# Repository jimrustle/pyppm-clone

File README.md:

#

This project is a modern update of [https://github.com/geekysuavo/pyppm](https://github.com/geekysuavo/pyppm).

All design credits go to geekysuavo.

see kicad/ppm-clone.pdf for schematic

# Changes

This project implements pyppm ver 2.2 in KiCAD 10.0 instead of gEDA.

- The CTX02-13665 and LT3439 have been replaced with a Wurth 78931812512 and TI SN6505BDBV due to the CTX02 becoming obsoleted

# Notes

No changes so far. Any parts changes will be performed in separate branches.

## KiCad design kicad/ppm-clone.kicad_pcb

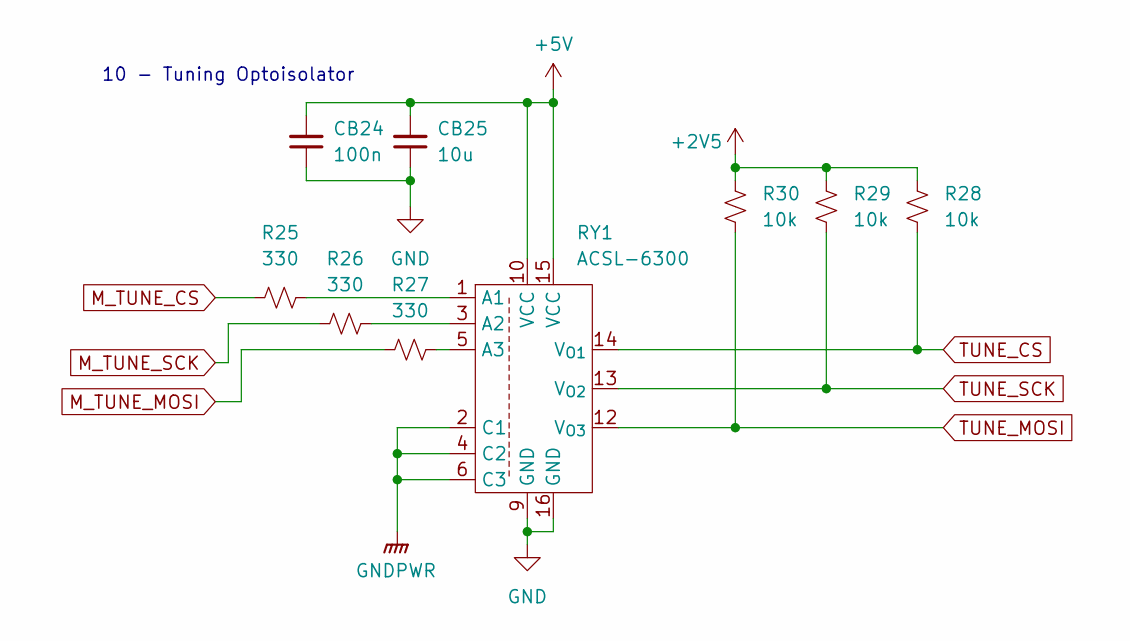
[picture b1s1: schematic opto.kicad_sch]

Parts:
CB24: 100n; C_0603_1608Metric_Pad1.08x0.95mm_HandSolder
CB25: 10u; C_0603_1608Metric_Pad1.08x0.95mm_HandSolder
R25, R26, R27: 330; R_0603_1608Metric_Pad0.98x0.95mm_HandSolder
R28, R29, R30: 10k; R_0603_1608Metric_Pad0.98x0.95mm_HandSolder
RY1: ACSL-6300; SO-16_3.9x9.9mm_P1.27mm

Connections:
+2V5: R28.1, R29.1, R30.1; also elsewhere on the board
+5V: CB24.2, CB25.2, RY1.10 (VCC), RY1.15 (VCC); also elsewhere on the board
GND: CB24.1, CB25.1, RY1.9 (GND), RY1.16 (GND); also elsewhere on the board
GNDPWR: RY1.2 (C1), RY1.4 (C2), RY1.6 (C3); also elsewhere on the board
M_TUNE_CS: R25.2; also elsewhere on the board
M_TUNE_MOSI: R27.2; also elsewhere on the board
M_TUNE_SCK: R26.2; also elsewhere on the board
unnamed: R25.1, RY1.1 (A1)
unnamed: R26.1, RY1.3 (A2)
unnamed: R27.1, RY1.5 (A3)
TUNE_CS: R28.2, RY1.14 (V_{O1}); also elsewhere on the board
TUNE_MOSI: R30.2, RY1.12 (V_{O3}); also elsewhere on the board
TUNE_SCK: R29.2, RY1.13 (V_{O2}); also elsewhere on the board

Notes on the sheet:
10 - Tuning Optoisolator

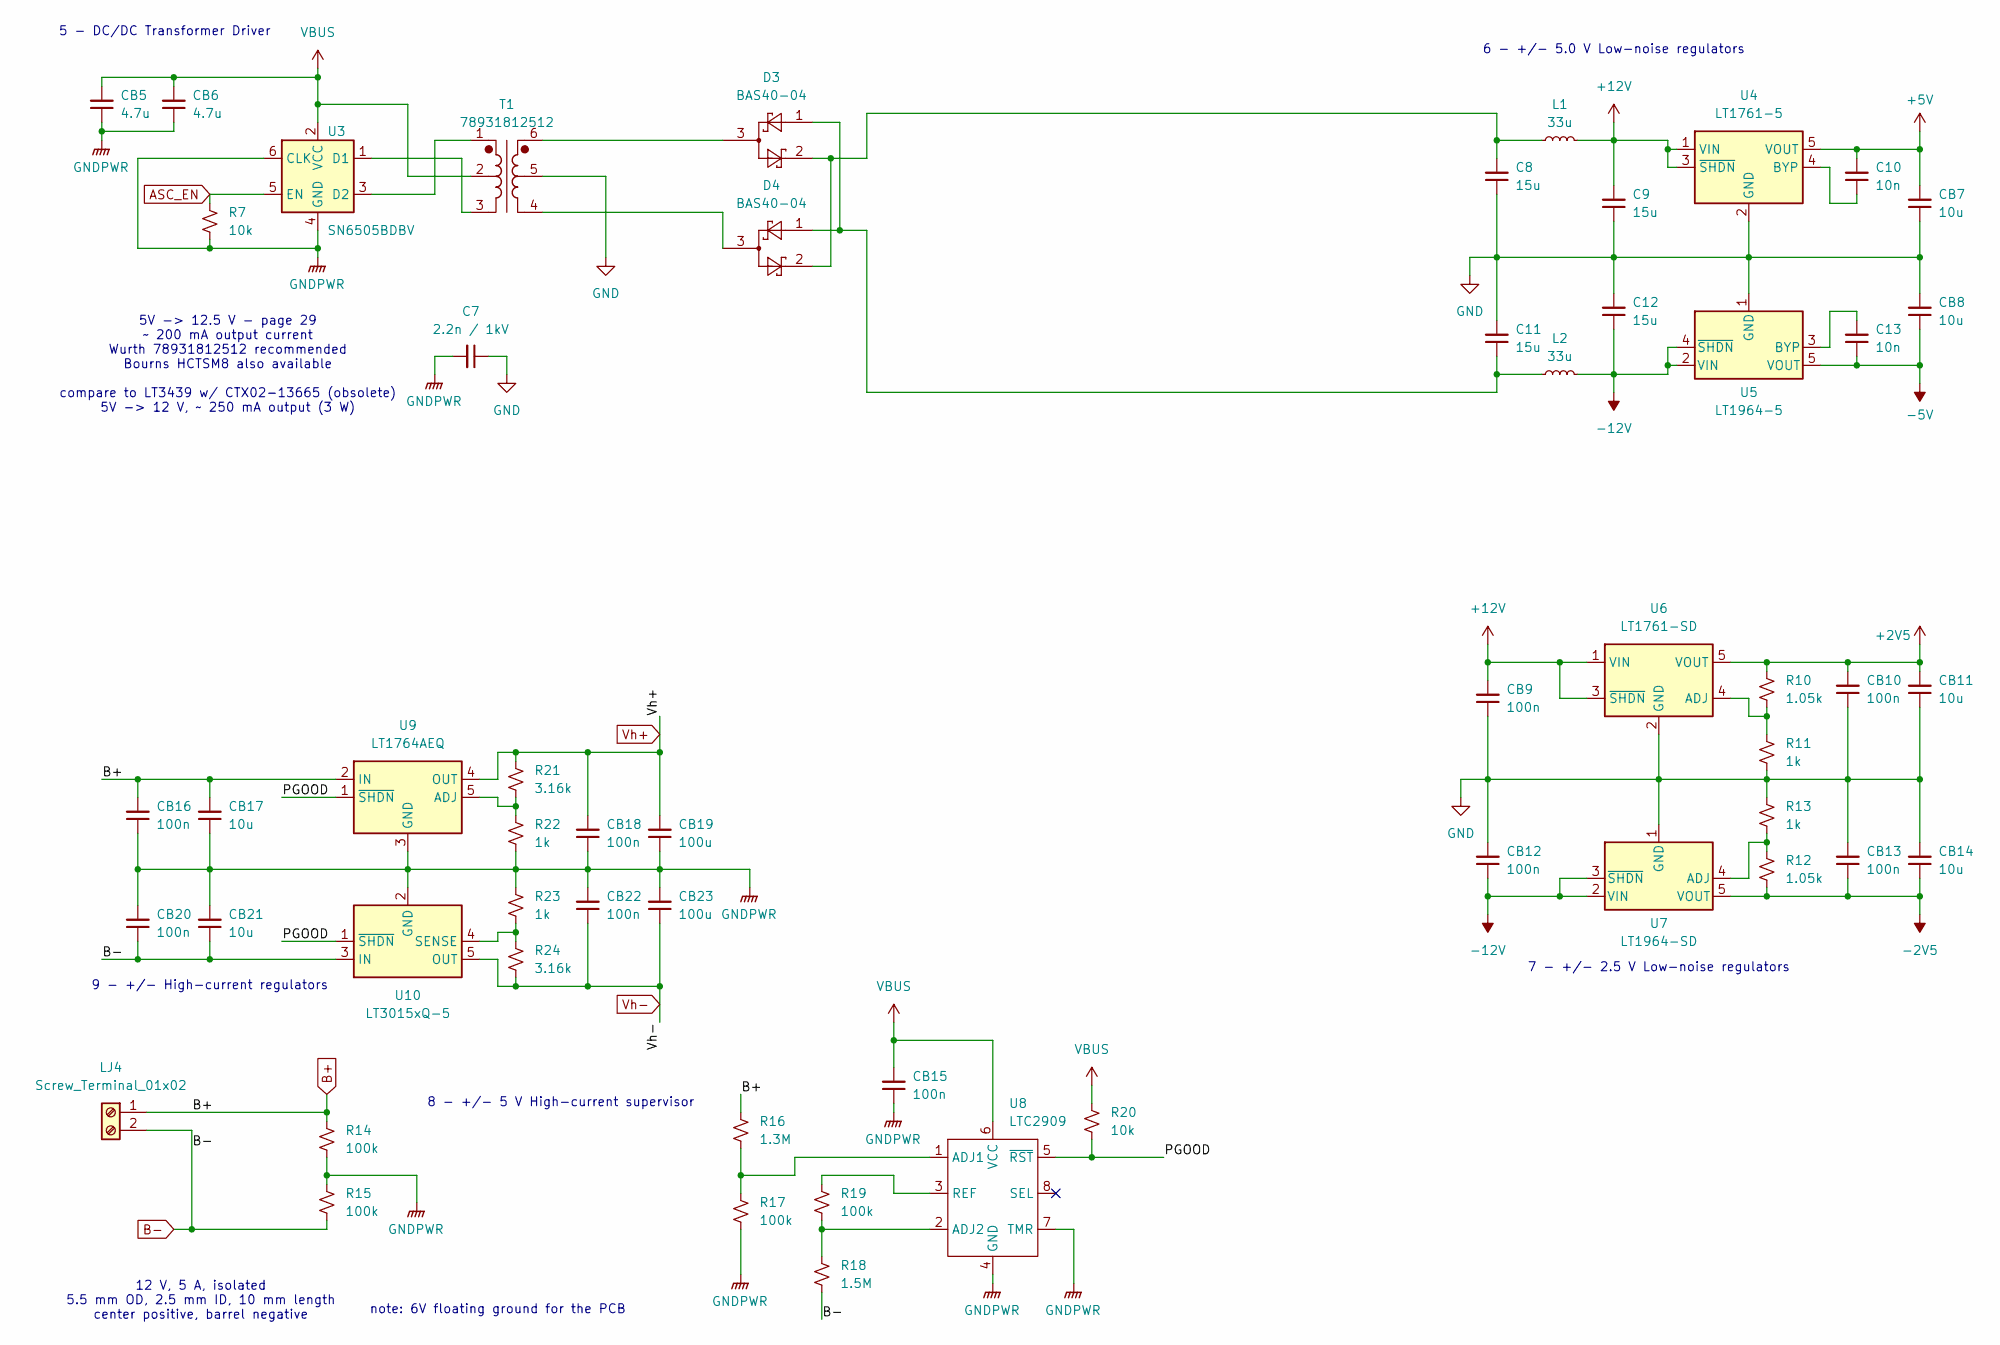
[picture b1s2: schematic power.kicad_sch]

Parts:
C7: 2.2n / 1kV; C_1206_3216Metric_Pad1.33x1.80mm_HandSolder
C8, C9, C11, C12: 15u; C_2220_5750Metric_Pad1.97x5.40mm_HandSolder
C10, C13: 10n; C_0603_1608Metric_Pad1.08x0.95mm_HandSolder
CB5, CB6: 4.7u; C_0603_1608Metric_Pad1.08x0.95mm_HandSolder
CB7, CB8, CB11, CB14, CB17, CB21: 10u; C_0603_1608Metric_Pad1.08x0.95mm_HandSolder
CB9, CB10, CB12, CB13, CB15, CB16, CB18, CB20, CB22: 100n; C_0603_1608Metric_Pad1.08x0.95mm_HandSolder
CB19, CB23: 100u; CP_Elec_5x5.3
D3, D4: BAS40-04; SOT-23
L1, L2: 33u; SDR6603
LJ4: Screw_Terminal_01x02; TerminalBlock_bornier-2_P5.08mm
R7, R20: 10k; R_0603_1608Metric_Pad0.98x0.95mm_HandSolder
R10, R12: 1.05k; R_0603_1608Metric_Pad0.98x0.95mm_HandSolder
R11, R13, R22, R23: 1k; R_0603_1608Metric_Pad0.98x0.95mm_HandSolder
R14, R15, R17, R19: 100k; R_0603_1608Metric_Pad0.98x0.95mm_HandSolder
R16: 1.3M; R_0603_1608Metric_Pad0.98x0.95mm_HandSolder
R18: 1.5M; R_0603_1608Metric_Pad0.98x0.95mm_HandSolder
R21, R24: 3.16k; R_0603_1608Metric_Pad0.98x0.95mm_HandSolder
T1: 78931812512; Transformer_Wuerth_750315371
U3: SN6505BDBV; SOT-23-6
U4: LT1761-5; TSOT-23-5
U5: LT1964-5; TSOT-23-5
U6: LT1761-SD; TSOT-23-5
U7: LT1964-SD; TSOT-23-5
U8: LTC2909; TSOT-23-8_HandSoldering
U9: LT1764AEQ; TO-263-5_TabPin3
U10: LT3015xQ-5; TO-263-5_TabPin3

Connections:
+2V5: CB10.2, CB11.2, R10.1, U6.5 (VOUT); also elsewhere on the board
+5V: C10.2, CB7.2, U4.5 (VOUT); also elsewhere on the board
+12V: C9.2, CB9.2, L1.2, U4.1 (VIN), U4.3 (~SHDN), U6.1 (VIN), U6.3 (~SHDN)
-2V5: CB13.1, CB14.1, R12.2, U7.5 (VOUT); also elsewhere on the board
-5V: C13.1, CB8.1, U5.5 (VOUT); also elsewhere on the board
-12V: C12.1, CB12.1, L2.2, U5.2 (VIN), U5.4 (~SHDN), U7.2 (VIN), U7.3 (~SHDN)
/power/PGOOD: R20.2, U8.5 (~RST), U9.1 (~SHDN), U10.1 (~SHDN)
ASC_EN: R7.1, U3.5 (EN); also elsewhere on the board
B+: CB16.2, CB17.2, LJ4.1, R14.1, R16.1, U9.2 (IN); also elsewhere on the board
B-: CB20.1, CB21.1, LJ4.2, R15.2, R18.2, U10.3 (IN)
GND: C7.1, C8.1, C9.1, C11.2, C12.2, CB7.1, CB8.2, CB9.1, CB10.1, CB11.1, CB12.2, CB13.2, CB14.2, R11.2, R13.1, T1.5, U4.2 (GND), U5.1 (GND), U6.2 (GND), U7.1 (GND); also elsewhere on the board
GNDPWR: C7.2, CB5.1, CB6.1, CB15.1, CB16.1, CB17.1, CB18.1, CB19.1, CB20.2, CB21.2, CB22.2, CB23.2, R7.2, R14.2, R15.1, R17.2, R22.2, R23.1, U3.4 (GND), U3.6 (CLK), U8.4 (GND), U8.7 (TMR), U9.3 (GND), U10.2 (GND); also elsewhere on the board
unnamed: C8.2, D3.2, D4.2, L1.1
unnamed: C11.1, D3.1, D4.1, L2.1
unnamed: D3.3, T1.6
unnamed: D4.3, T1.4
unnamed: T1.3, U3.1 (D1)
unnamed: T1.1, U3.3 (D2)
unnamed: C10.1, U4.4 (BYP)
unnamed: C13.2, U5.3 (BYP)
unnamed: R10.2, R11.1, U6.4 (ADJ)
unnamed: R12.1, R13.2, U7.4 (ADJ)
unnamed: R16.2, R17.1, U8.1 (ADJ1)
unnamed: R18.1, R19.2, U8.2 (ADJ2)
unnamed: R19.1, U8.3 (REF)
unnamed: R21.2, R22.1, U9.5 (ADJ)
unnamed: R23.2, R24.1, U10.4 (SENSE)
VBUS: CB5.2, CB6.2, CB15.2, R20.1, T1.2, U3.2 (VCC), U8.6 (VCC); also elsewhere on the board
Vh+: CB18.2, CB19.2, R21.1, U9.4 (OUT); also elsewhere on the board
Vh-: CB22.1, CB23.1, R24.2, U10.5 (OUT); also elsewhere on the board

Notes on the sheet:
8 - +/- 5 V High-current supervisor
9 - +/- High-current regulators
5V -> 12.5 V - page 29 ~ 200 mA output current Wurth 78931812512 recommended Bourns HCTSM8 also available compare to LT3439 w/ CTX02-13665 (obsolete) 5V -> 12 V, ~ 250 mA output (3 W)
7 - +/- 2.5 V Low-noise regulators
5 - DC/DC Transformer Driver
12 V, 5 A, isolated 5.5 mm OD, 2.5 mm ID, 10 mm length center positive, barrel negative
note: 6V floating ground for the PCB
6 - +/- 5.0 V Low-noise regulators

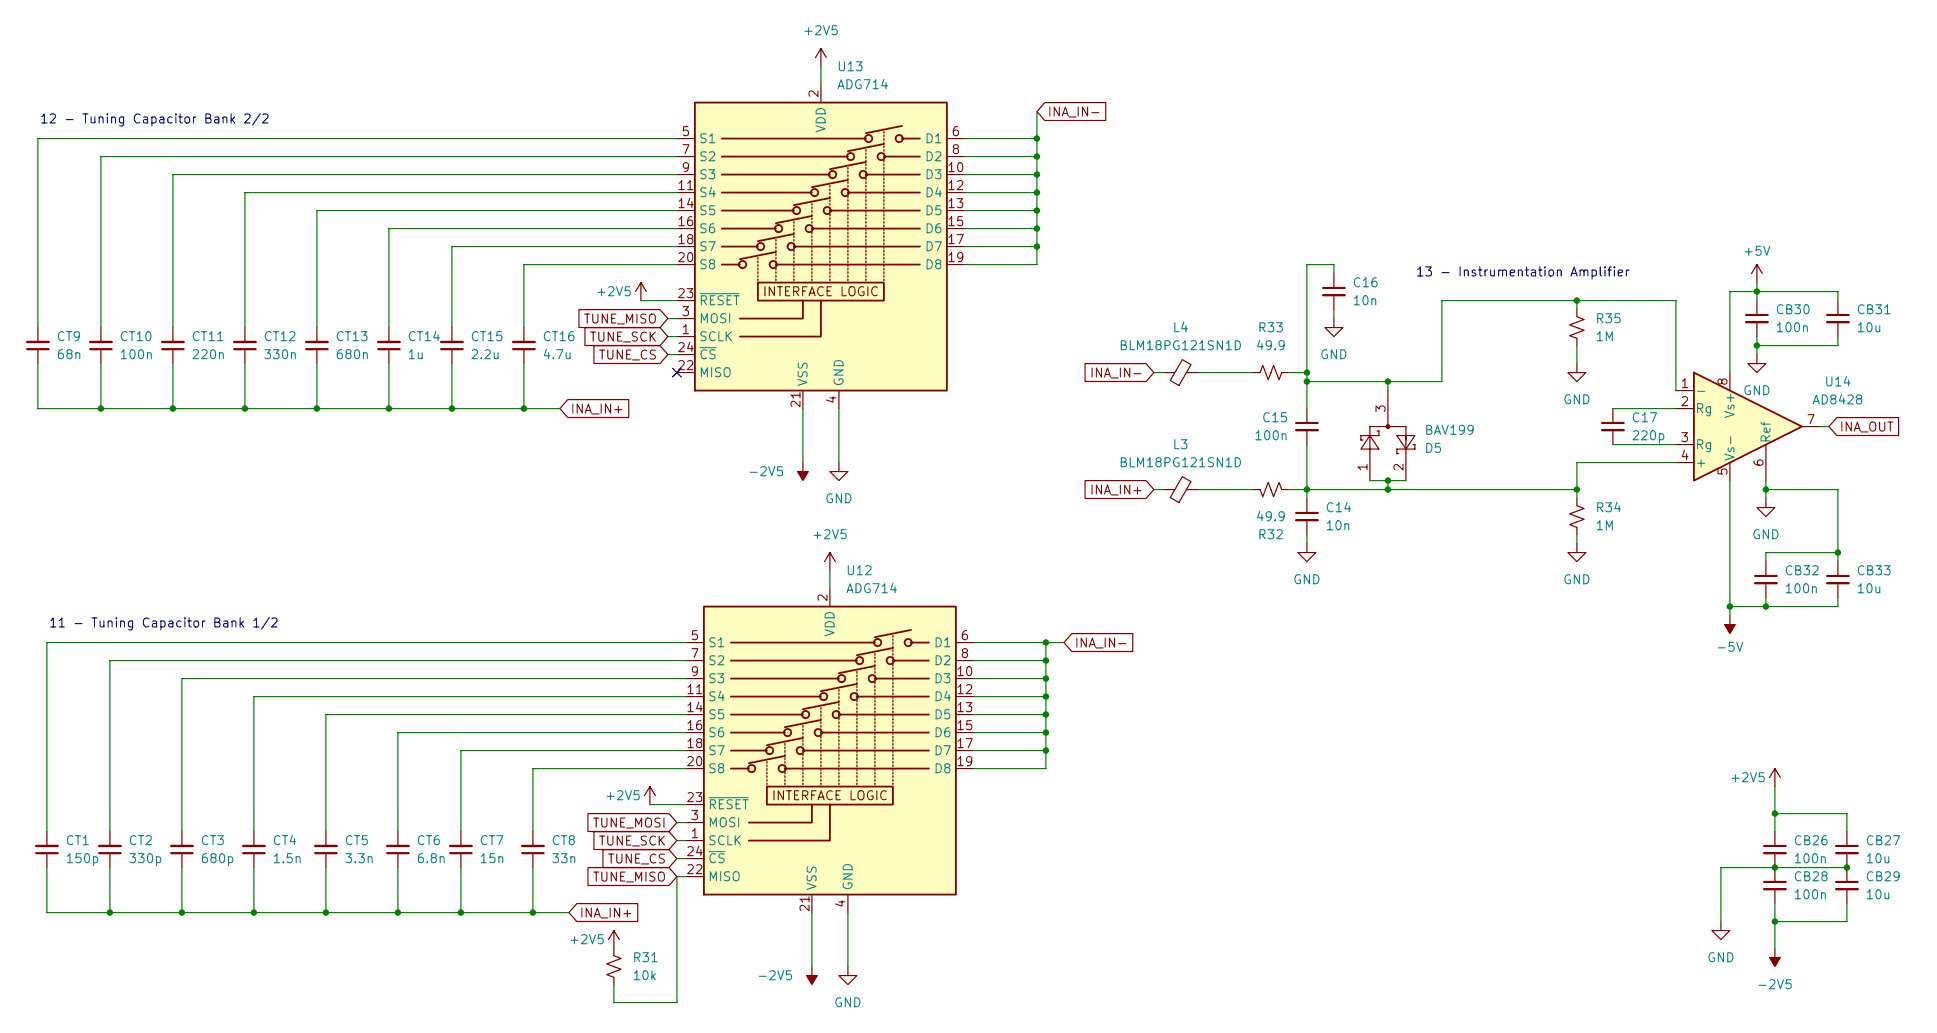
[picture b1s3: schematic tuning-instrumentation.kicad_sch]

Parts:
C14, C16: 10n; C_0603_1608Metric_Pad1.08x0.95mm_HandSolder
C15: 100n; C_0603_1608Metric_Pad1.08x0.95mm_HandSolder
C17: 220p; C_0603_1608Metric_Pad1.08x0.95mm_HandSolder
CB26, CB28, CB30, CB32: 100n; C_0603_1608Metric_Pad1.08x0.95mm_HandSolder
CB27, CB29, CB31, CB33: 10u; C_0603_1608Metric_Pad1.08x0.95mm_HandSolder
CT1: 150p; C_0603_1608Metric_Pad1.08x0.95mm_HandSolder
CT2: 330p; C_0603_1608Metric_Pad1.08x0.95mm_HandSolder
CT3: 680p; C_0603_1608Metric_Pad1.08x0.95mm_HandSolder
CT4: 1.5n; C_0603_1608Metric_Pad1.08x0.95mm_HandSolder
CT5: 3.3n; C_0603_1608Metric_Pad1.08x0.95mm_HandSolder
CT6: 6.8n; C_0603_1608Metric_Pad1.08x0.95mm_HandSolder
CT7: 15n; C_0603_1608Metric_Pad1.08x0.95mm_HandSolder
CT8: 33n; C_0603_1608Metric_Pad1.08x0.95mm_HandSolder
CT9: 68n; C_0603_1608Metric_Pad1.08x0.95mm_HandSolder
CT10: 100n; C_0603_1608Metric_Pad1.08x0.95mm_HandSolder
CT11: 220n; C_0603_1608Metric_Pad1.08x0.95mm_HandSolder
CT12: 330n; C_0603_1608Metric_Pad1.08x0.95mm_HandSolder
CT13: 680n; C_0603_1608Metric_Pad1.08x0.95mm_HandSolder
CT14: 1u; C_0603_1608Metric_Pad1.08x0.95mm_HandSolder
CT15: 2.2u; C_0603_1608Metric_Pad1.08x0.95mm_HandSolder
CT16: 4.7u; C_0603_1608Metric_Pad1.08x0.95mm_HandSolder
D5: BAV199; SOT-23
L3, L4: BLM18PG121SN1D; L_0603_1608Metric_Pad1.05x0.95mm_HandSolder
R31: 10k; R_0603_1608Metric_Pad0.98x0.95mm_HandSolder
R32, R33: 49.9; R_0603_1608Metric_Pad0.98x0.95mm_HandSolder
R34, R35: 1M; R_0603_1608Metric_Pad0.98x0.95mm_HandSolder
U12, U13: ADG714; TSSOP-24_4.4x7.8mm_P0.65mm
U14: AD8428; SOIC-8_3.9x4.9mm_P1.27mm

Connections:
+2V5: CB26.1, CB27.1, R31.2, U12.2 (VDD), U12.23 (~RESET), U13.2 (VDD), U13.23 (~RESET); also elsewhere on the board
+5V: CB30.1, CB31.1, U14.8 (Vs+); also elsewhere on the board
-2V5: CB28.2, CB29.2, U12.21 (VSS), U13.21 (VSS); also elsewhere on the board
-5V: CB32.2, CB33.2, U14.5 (Vs-); also elsewhere on the board
GND: C14.2, C16.2, CB26.2, CB27.2, CB28.1, CB29.1, CB30.2, CB31.2, CB32.1, CB33.1, R34.2, R35.2, U12.4 (GND), U13.4 (GND), U14.6 (Ref); also elsewhere on the board
INA_IN+: CT1.1, CT2.1, CT3.1, CT4.1, CT5.1, CT6.1, CT7.1, CT8.1, CT9.1, CT10.1, CT11.1, CT12.1, CT13.1, CT14.1, CT15.1, CT16.1, L3.1; also elsewhere on the board
INA_IN-: L4.1, U12.6 (D1), U12.8 (D2), U12.10 (D3), U12.12 (D4), U12.13 (D5), U12.15 (D6), U12.17 (D7), U12.19 (D8), U13.6 (D1), U13.8 (D2), U13.10 (D3), U13.12 (D4), U13.13 (D5), U13.15 (D6), U13.17 (D7), U13.19 (D8); also elsewhere on the board
INA_OUT: U14.7; also elsewhere on the board
unnamed: C17.1, U14.2 (Rg)
unnamed: C17.2, U14.3 (Rg)
unnamed: L3.2, R32.1
unnamed: L4.2, R33.1
unnamed: CT1.2, U12.5 (S1)
unnamed: CT2.2, U12.7 (S2)
unnamed: CT3.2, U12.9 (S3)
unnamed: CT4.2, U12.11 (S4)
unnamed: CT5.2, U12.14 (S5)
unnamed: CT6.2, U12.16 (S6)
unnamed: CT7.2, U12.18 (S7)
unnamed: CT8.2, U12.20 (S8)
unnamed: CT9.2, U13.5 (S1)
unnamed: CT10.2, U13.7 (S2)
unnamed: CT11.2, U13.9 (S3)
unnamed: CT12.2, U13.11 (S4)
unnamed: CT13.2, U13.14 (S5)
unnamed: CT14.2, U13.16 (S6)
unnamed: CT15.2, U13.18 (S7)
unnamed: CT16.2, U13.20 (S8)
unnamed: C14.1, C15.2, D5.1, D5.2, R32.2, R34.1, U14.4 (+)
unnamed: C15.1, C16.1, D5.3, R33.2, R35.1, U14.1 (-)
TUNE_CS: U12.24 (~CS), U13.24 (~CS); also elsewhere on the board
TUNE_MISO: R31.1, U12.22 (MISO), U13.3 (MOSI)
TUNE_MOSI: U12.3 (MOSI); also elsewhere on the board
TUNE_SCK: U12.1 (SCLK), U13.1 (SCLK); also elsewhere on the board

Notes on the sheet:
12 - Tuning Capacitor Bank 2/2
13 - Instrumentation Amplifier
11 - Tuning Capacitor Bank 1/2

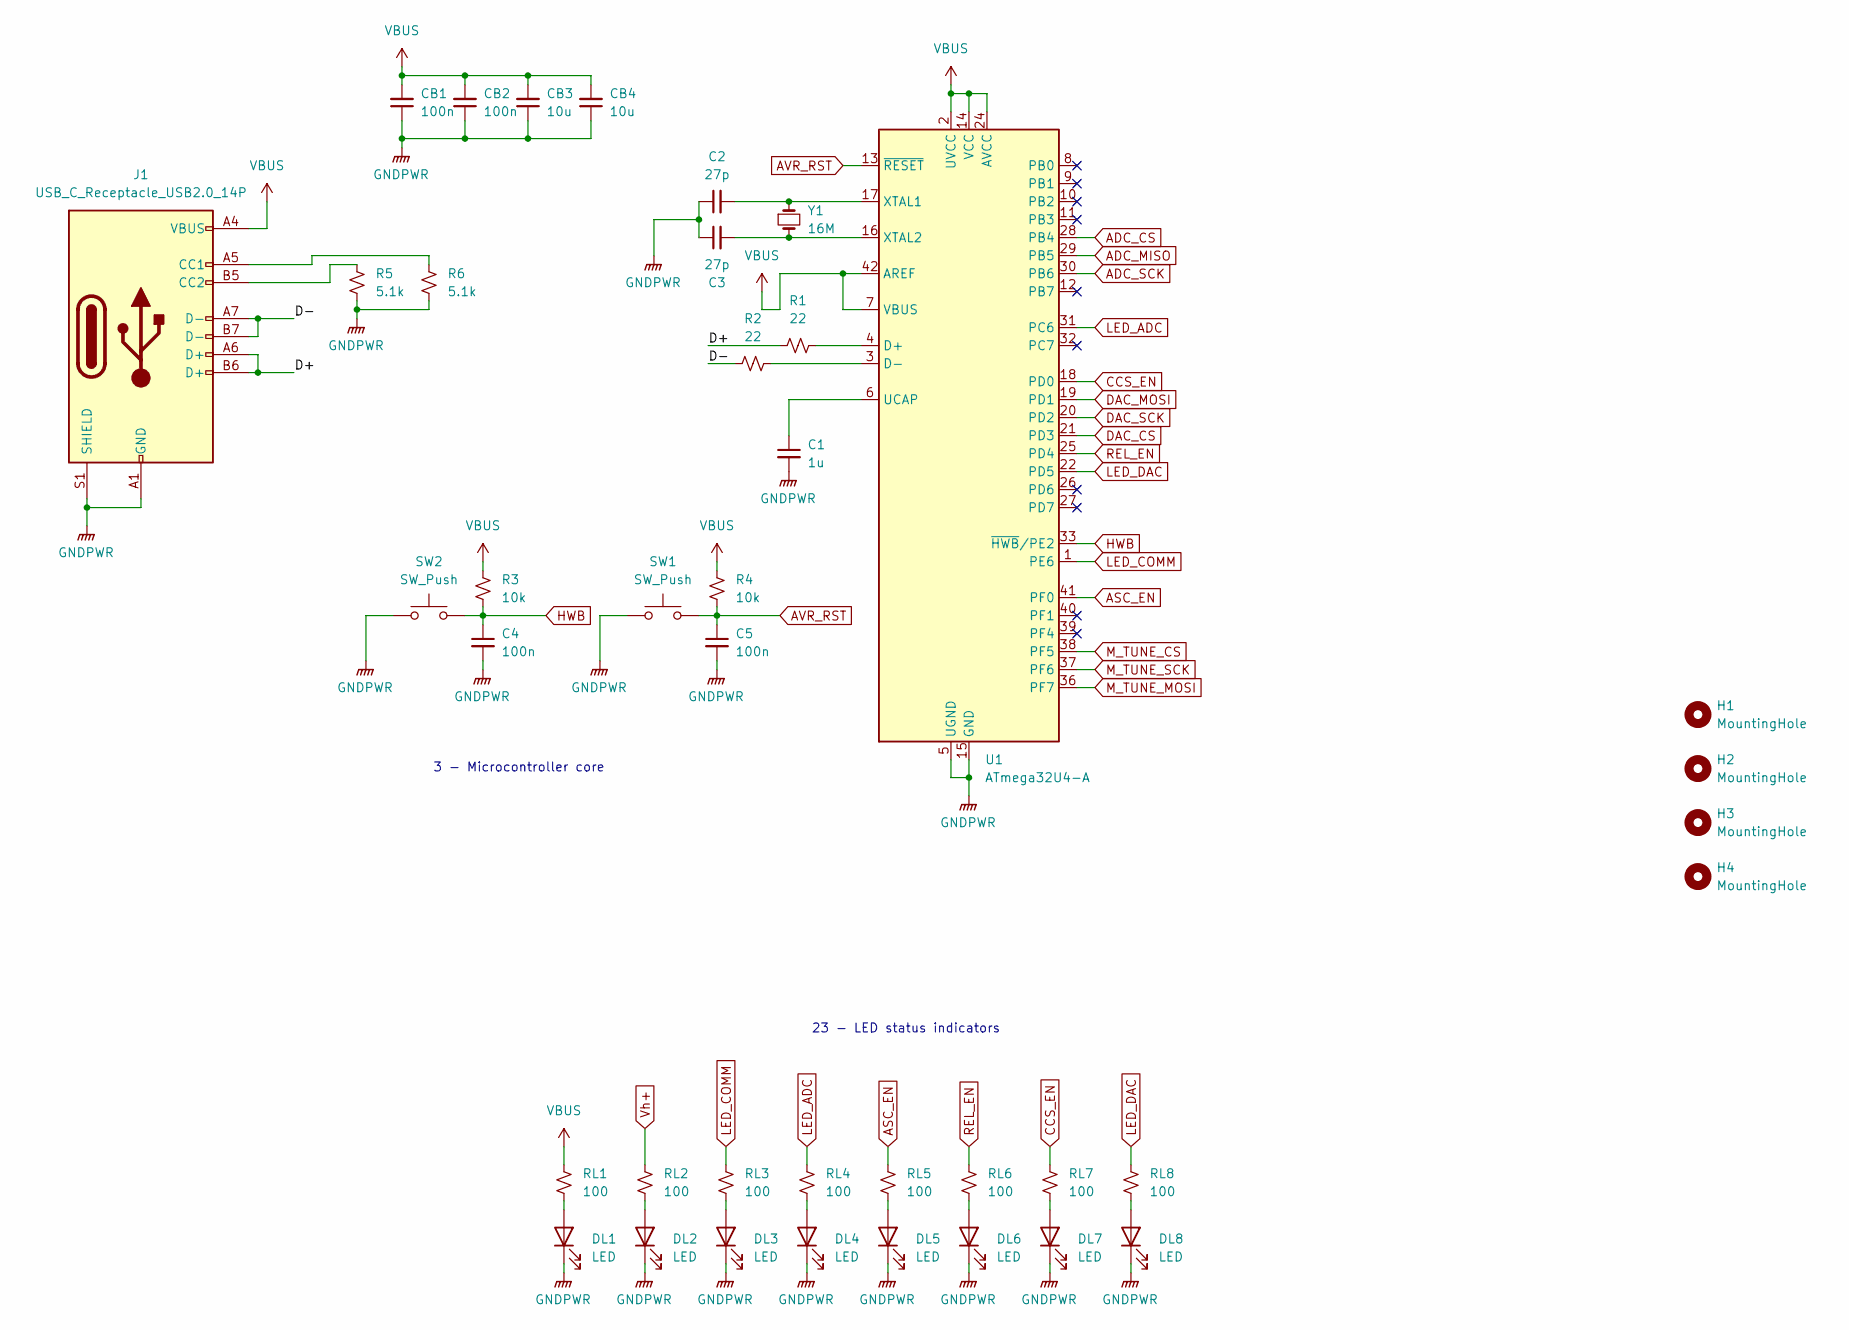
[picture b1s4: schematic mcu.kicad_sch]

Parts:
C1: 1u; C_0603_1608Metric_Pad1.08x0.95mm_HandSolder
C2, C3: 27p; C_0603_1608Metric_Pad1.08x0.95mm_HandSolder
C4, C5: 100n; C_0603_1608Metric_Pad1.08x0.95mm_HandSolder
CB1, CB2: 100n; C_0603_1608Metric_Pad1.08x0.95mm_HandSolder
CB3, CB4: 10u; C_0603_1608Metric_Pad1.08x0.95mm_HandSolder
DL1, DL2, DL3, DL4, DL5, DL6, DL7, DL8: LED; LED_0603_1608Metric_Pad1.05x0.95mm_HandSolder
H1, H2, H3, H4: MountingHole; MountingHole_3.2mm_M3_ISO7380_Pad
J1: USB_C_Receptacle_USB2.0_14P; USB_C_Receptacle_HCTL_HC-TYPE-C-16P-01A
R1, R2: 22; R_0603_1608Metric_Pad0.98x0.95mm_HandSolder
R3, R4: 10k; R_0603_1608Metric_Pad0.98x0.95mm_HandSolder
R5, R6: 5.1k; R_0603_1608Metric_Pad0.98x0.95mm_HandSolder
RL1, RL2, RL3, RL4, RL5, RL6, RL7, RL8: 100; R_0603_1608Metric_Pad0.98x0.95mm_HandSolder
SW1, SW2: SW_Push; SW_SPST_B3S-1000
U1: ATmega32U4-A; TQFP-44_10x10mm_P0.8mm
Y1: 16M; Crystal_SMD_Abracon_ABM7-2Pin_6.0x3.5mm

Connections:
/mcu/D+: J1.A6 (D+), J1.B6 (D+), R1.2
/mcu/D-: J1.A7 (D-), J1.B7 (D-), R2.2
ADC_CS: U1.28 (PB4); also elsewhere on the board
ADC_MISO: U1.29 (PB5); also elsewhere on the board
ADC_SCK: U1.30 (PB6); also elsewhere on the board
ASC_EN: RL5.1, U1.41 (PF0); also elsewhere on the board
AVR_RST: C5.1, R4.2, SW1.2, U1.13 (~RESET)
CCS_EN: RL7.1, U1.18 (PD0); also elsewhere on the board
DAC_CS: U1.21 (PD3); also elsewhere on the board
DAC_MOSI: U1.19 (PD1); also elsewhere on the board
DAC_SCK: U1.20 (PD2); also elsewhere on the board
GNDPWR: C1.2, C2.1, C3.1, C4.2, C5.2, CB1.1, CB2.1, CB3.1, CB4.1, DL1.1 (K), DL2.1 (K), DL3.1 (K), DL4.1 (K), DL5.1 (K), DL6.1 (K), DL7.1 (K), DL8.1 (K), J1.A1 (GND), J1.A12 (GND), J1.B1 (GND), J1.B12 (GND), J1.S1 (SHIELD), R5.2, R6.2, SW1.1, SW2.1, U1.5 (UGND), U1.15 (GND), U1.23 (GND), U1.35 (GND), U1.43 (GND); also elsewhere on the board
HWB: C4.1, R3.2, SW2.2, U1.33 (~HWB/PE2)
LED_ADC: RL4.1, U1.31 (PC6)
LED_COMM: RL3.1, U1.1 (PE6)
LED_DAC: RL8.1, U1.22 (PD5)
M_TUNE_CS: U1.38 (PF5); also elsewhere on the board
M_TUNE_MOSI: U1.36 (PF7); also elsewhere on the board
M_TUNE_SCK: U1.37 (PF6); also elsewhere on the board
unnamed: DL1.2 (A), RL1.2
unnamed: DL2.2 (A), RL2.2
unnamed: DL3.2 (A), RL3.2
unnamed: DL4.2 (A), RL4.2
unnamed: DL5.2 (A), RL5.2
unnamed: DL6.2 (A), RL6.2
unnamed: DL7.2 (A), RL7.2
unnamed: DL8.2 (A), RL8.2
unnamed: J1.A5 (CC1), R6.1
unnamed: J1.B5 (CC2), R5.1
unnamed: R1.1, U1.4 (D+)
unnamed: R2.1, U1.3 (D-)
unnamed: C1.1, U1.6 (UCAP)
unnamed: C2.2, U1.17 (XTAL1), Y1.1
unnamed: C3.2, U1.16 (XTAL2), Y1.2
REL_EN: RL6.1, U1.25 (PD4); also elsewhere on the board
VBUS: CB1.2, CB2.2, CB3.2, CB4.2, J1.A4 (VBUS), J1.A9 (VBUS), J1.B4 (VBUS), J1.B9 (VBUS), R3.1, R4.1, RL1.1, U1.2 (UVCC), U1.7 (VBUS), U1.14 (VCC), U1.24 (AVCC), U1.34 (VCC), U1.42 (AREF), U1.44 (AVCC); also elsewhere on the board
Vh+: RL2.1; also elsewhere on the board

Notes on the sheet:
23 - LED status indicators
3 - Microcontroller core

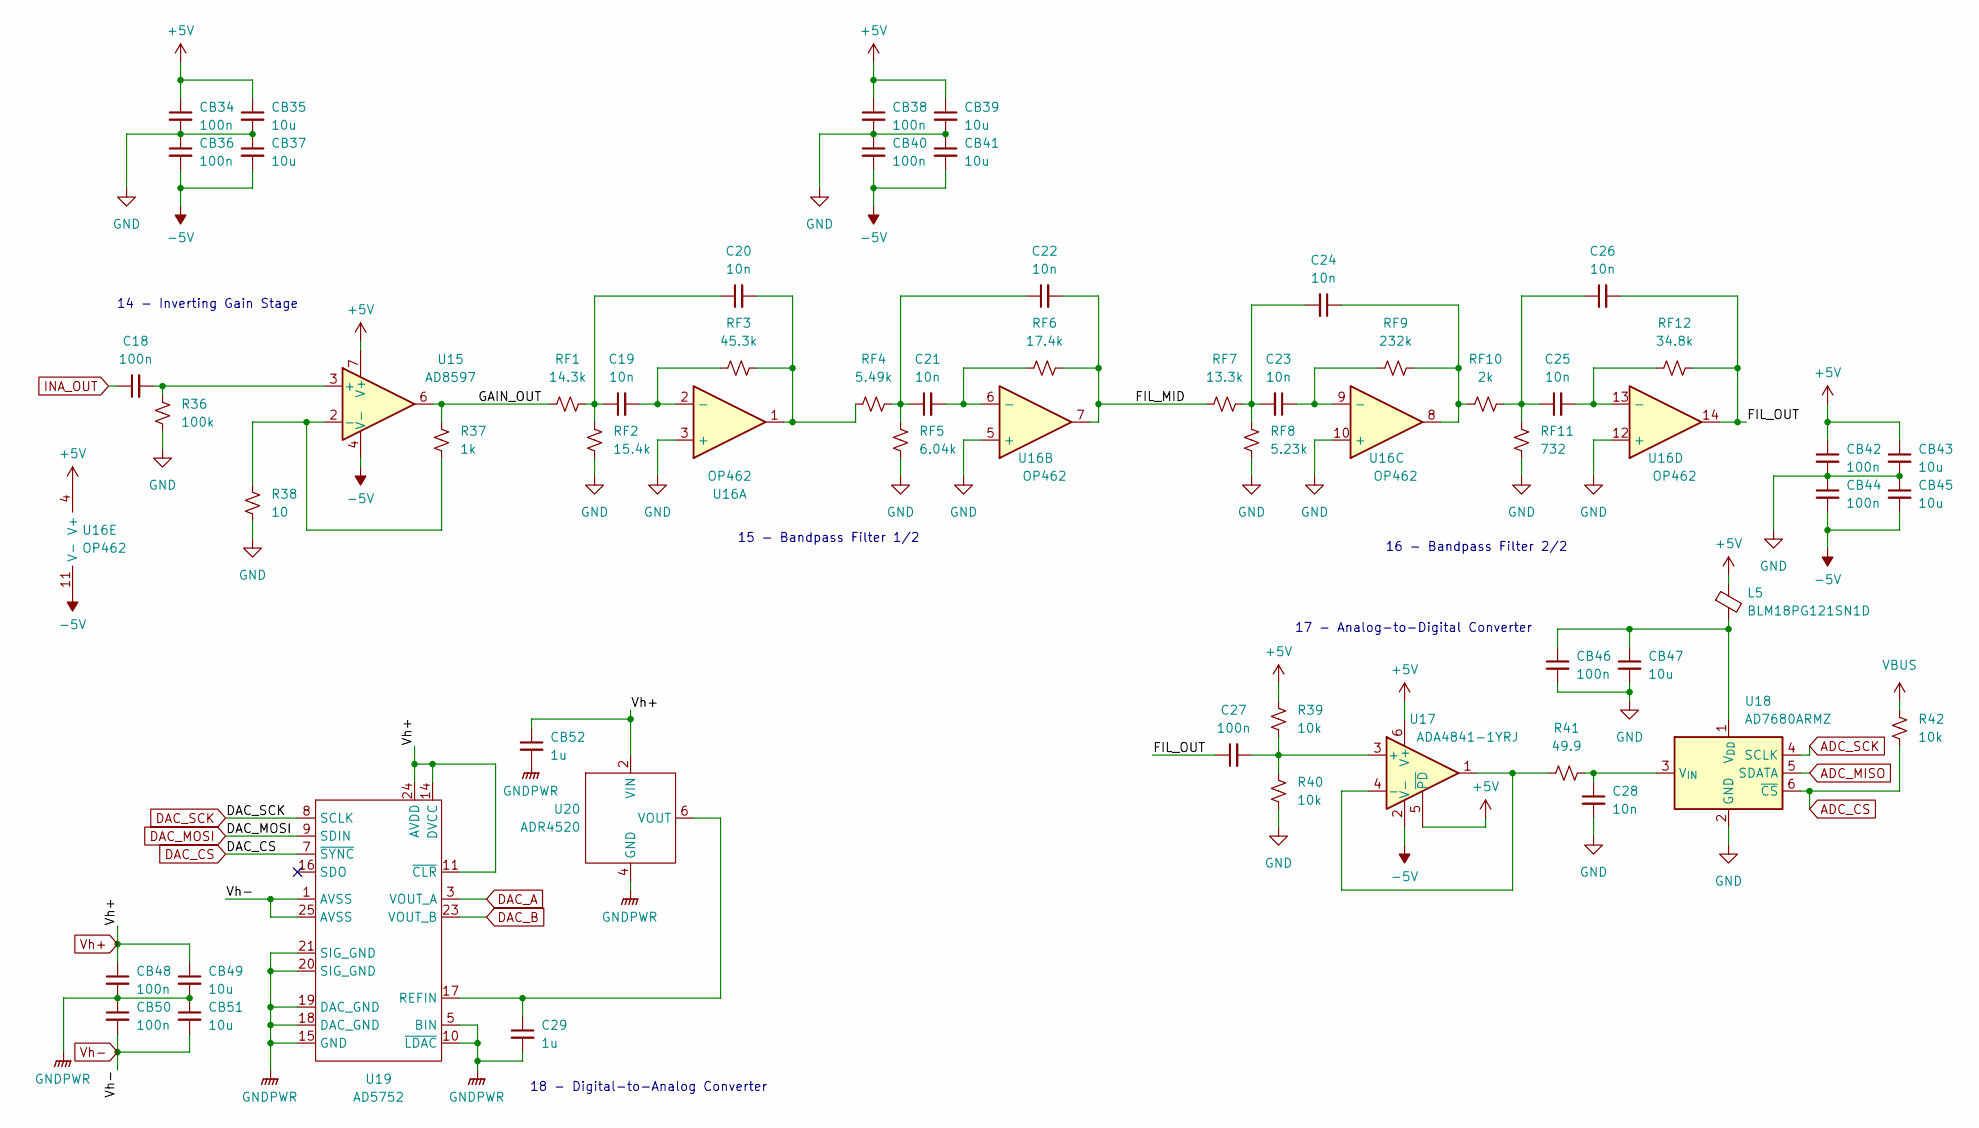
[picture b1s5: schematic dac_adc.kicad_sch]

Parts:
C18, C27: 100n; C_0603_1608Metric_Pad1.08x0.95mm_HandSolder
C19, C20, C21, C22, C23, C24, C25, C26, C28: 10n; C_0603_1608Metric_Pad1.08x0.95mm_HandSolder
C29: 1u; C_0603_1608Metric_Pad1.08x0.95mm_HandSolder
CB34, CB36, CB38, CB40, CB42, CB44, CB46, CB48, CB50: 100n; C_0603_1608Metric_Pad1.08x0.95mm_HandSolder
CB35, CB37, CB39, CB41, CB43, CB45, CB47, CB49, CB51: 10u; C_0603_1608Metric_Pad1.08x0.95mm_HandSolder
CB52: 1u; C_0603_1608Metric_Pad1.08x0.95mm_HandSolder
L5: BLM18PG121SN1D; L_0603_1608Metric_Pad1.05x0.95mm_HandSolder
R36: 100k; R_0603_1608Metric_Pad0.98x0.95mm_HandSolder
R37: 1k; R_0603_1608Metric_Pad0.98x0.95mm_HandSolder
R38: 10; R_0603_1608Metric_Pad0.98x0.95mm_HandSolder
R39, R40, R42: 10k; R_0603_1608Metric_Pad0.98x0.95mm_HandSolder
R41: 49.9; R_0603_1608Metric_Pad0.98x0.95mm_HandSolder
RF1: 14.3k; R_0603_1608Metric_Pad0.98x0.95mm_HandSolder
RF2: 15.4k; R_0603_1608Metric_Pad0.98x0.95mm_HandSolder
RF3: 45.3k; R_0603_1608Metric_Pad0.98x0.95mm_HandSolder
RF4: 5.49k; R_0603_1608Metric_Pad0.98x0.95mm_HandSolder
RF5: 6.04k; R_0603_1608Metric_Pad0.98x0.95mm_HandSolder
RF6: 17.4k; R_0603_1608Metric_Pad0.98x0.95mm_HandSolder
RF7: 13.3k; R_0603_1608Metric_Pad0.98x0.95mm_HandSolder
RF8: 5.23k; R_0603_1608Metric_Pad0.98x0.95mm_HandSolder
RF9: 232k; R_0603_1608Metric_Pad0.98x0.95mm_HandSolder
RF10: 2k; R_0603_1608Metric_Pad0.98x0.95mm_HandSolder
RF11: 732; R_0603_1608Metric_Pad0.98x0.95mm_HandSolder
RF12: 34.8k; R_0603_1608Metric_Pad0.98x0.95mm_HandSolder
U15: AD8597; SOIC-8_3.9x4.9mm_P1.27mm
U16: OP462; TSSOP-14_4.4x5mm_P0.65mm
U17: ADA4841-1YRJ; SOT-23-6
U18: AD7680ARMZ; SOT-23-6
U19: AD5752; HTSSOP-24-1EP_4.4x7.8mm_P0.65mm_EP3.2x5mm
U20: ADR4520; SOIC-8_3.9x4.9mm_P1.27mm

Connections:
+5V: CB34.1, CB35.1, CB38.1, CB39.1, CB42.1, CB43.1, L5.1, R39.1, U15.7 (V+), U16.4 (V+), U17.5 (~PD), U17.6 (V+); also elsewhere on the board
-5V: CB36.2, CB37.2, CB40.2, CB41.2, CB44.2, CB45.2, U15.4 (V-), U16.11 (V-), U17.2 (V-); also elsewhere on the board
/dac_adc/FIL_MID: C22.2, RF6.2, RF7.1, U16.7
/dac_adc/FIL_OUT: C26.2, C27.1, RF12.2, U16.14
/dac_adc/GAIN_OUT: R37.2, RF1.1, U15.6
ADC_CS: R42.2, U18.6 (~CS); also elsewhere on the board
ADC_MISO: U18.5 (SDATA); also elsewhere on the board
ADC_SCK: U18.4 (SCLK); also elsewhere on the board
DAC_A: U19.3 (VOUT_A); also elsewhere on the board
DAC_B: U19.23 (VOUT_B); also elsewhere on the board
DAC_CS: U19.7 (~SYNC); also elsewhere on the board
DAC_MOSI: U19.9 (SDIN); also elsewhere on the board
DAC_SCK: U19.8 (SCLK); also elsewhere on the board
GND: C28.2, CB34.2, CB35.2, CB36.1, CB37.1, CB38.2, CB39.2, CB40.1, CB41.1, CB42.2, CB43.2, CB44.1, CB45.1, CB46.2, CB47.2, R36.1, R38.1, R40.2, RF2.2, RF5.2, RF8.2, RF11.2, U16.3 (+), U16.5 (+), U16.10 (+), U16.12 (+), U18.2 (GND); also elsewhere on the board
GNDPWR: C29.2, CB48.2, CB49.2, CB50.1, CB51.1, CB52.2, U19.5 (BIN), U19.10 (~LDAC), U19.15 (GND), U19.18 (DAC_GND), U19.19 (DAC_GND), U19.20 (SIG_GND), U19.21 (SIG_GND), U20.4 (GND); also elsewhere on the board
INA_OUT: C18.1; also elsewhere on the board
unnamed: C19.1, C20.1, RF1.2, RF2.1
unnamed: C20.2, RF3.2, RF4.1, U16.1
unnamed: C21.1, C22.1, RF4.2, RF5.1
unnamed: C23.2, C24.2, RF7.2, RF8.1
unnamed: C24.1, RF9.2, RF10.1, U16.8
unnamed: C25.1, C26.1, RF10.2, RF11.1
unnamed: C18.2, R36.2, U15.3 (+)
unnamed: R37.1, R38.2, U15.2 (-)
unnamed: C19.2, RF3.1, U16.2 (-)
unnamed: C21.2, RF6.1, U16.6 (-)
unnamed: C23.1, RF9.1, U16.9 (-)
unnamed: C25.2, RF12.1, U16.13 (-)
unnamed: C27.2, R39.2, R40.1, U17.3 (+)
unnamed: R41.2, U17.1, U17.4 (-)
unnamed: CB46.1, CB47.1, L5.2, U18.1 (V_{DD})
unnamed: C28.1, R41.1, U18.3 (V_{IN})
unnamed: C29.1, U19.17 (REFIN), U20.6 (VOUT)
VBUS: R42.1; also elsewhere on the board
Vh+: CB48.1, CB49.1, CB52.1, U19.11 (~CLR), U19.14 (DVCC), U19.24 (AVDD), U20.2 (VIN); also elsewhere on the board
Vh-: CB50.2, CB51.2, U19.1 (AVSS), U19.25 (AVSS); also elsewhere on the board

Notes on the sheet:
18 - Digital-to-Analog Converter
14 - Inverting Gain Stage
15 - Bandpass Filter 1/2
17 - Analog-to-Digital Converter
16 - Bandpass Filter 2/2

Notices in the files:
kicad/ppm-clone.kicad_pcb:
License:
CC-BY-SA (pcb)
GNU GPL 3.0 (software)
